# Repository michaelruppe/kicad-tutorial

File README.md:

This is the repo we create in my [KiCad - Zero to Hero series](https://www.youtube.com/playlist?list=PLkjlwzY9yBVnLyYtGvQODO6tDs3WEyncr)

# Kicad Tutorial
*a nice little PCB*

 This is my PCB, there are many like it but this one is mine.

 ## Schematic

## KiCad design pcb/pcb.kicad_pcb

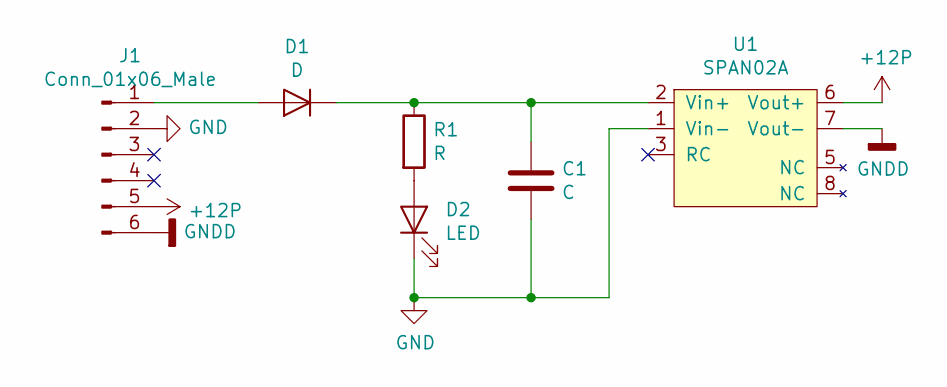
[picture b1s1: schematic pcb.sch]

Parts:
C1: C; C_0805_2012Metric
D1: D; D_SMA
D2: LED; LED_0805_2012Metric
J1: Conn_01x06_Male; Molex_Micro-Fit_3.0_43045-0612_2x03_P3.00mm_Vertical
R1: R; R_1206_3216Metric
U1: SPAN02A

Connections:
+12P: J1.5, U1.6 (Vout+)
GND: C1.2, D2.1 (K), J1.2, U1.1 (Vin-)
GNDD: J1.6, U1.7 (Vout-)
unnamed: C1.1, D1.1 (K), R1.1, U1.2 (Vin+)
unnamed: D1.2 (A), J1.1
unnamed: D2.2 (A), R1.2

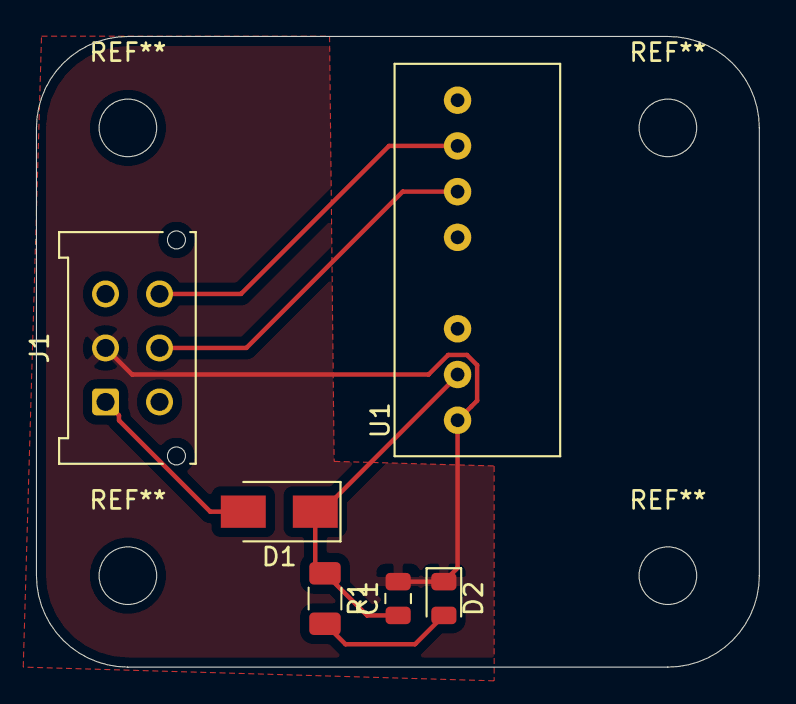
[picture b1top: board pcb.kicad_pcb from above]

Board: 2 copper layers, 40.2 x 35.0 mm, 6 parts (0 on the bottom side), 6 nets.

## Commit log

2020-05-02 :star: initial commit
2020-05-07 Update README.md
    Add link
